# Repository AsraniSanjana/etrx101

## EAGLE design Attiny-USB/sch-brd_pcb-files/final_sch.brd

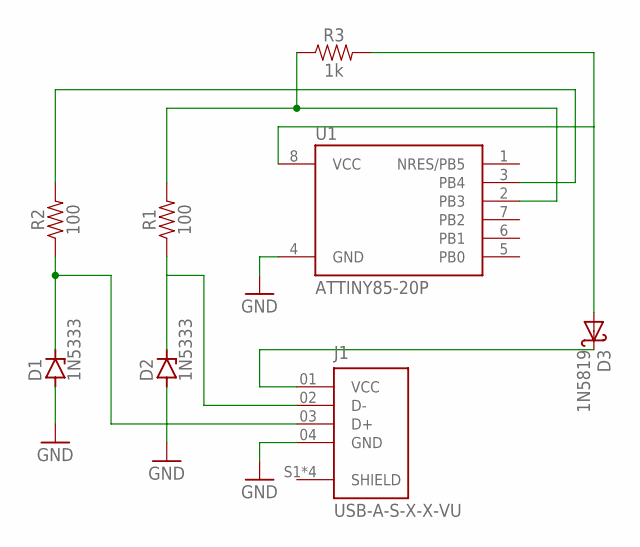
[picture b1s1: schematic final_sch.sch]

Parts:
D1, D2: 1N5333; C1702-15
D3: 1N5819; DO41-10
J1: USB-A-S-X-X-VU; SAMTEC_USB-A-S-X-X-VU
R1, R2: 100; AXIAL-0.3EZ
R3: 1k; AXIAL-0.3-KIT
U1: ATTINY85-20P; PDIP08_300MIL

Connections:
GND: D1.A, D2.A, J1.04 (GND), U1.4 (GND)
unnamed: D1.C, J1.03 (D+), R2.P$1 (1)
unnamed: D2.C, J1.02 (D-), R1.P$1 (1)
unnamed: R2.P$2 (2), U1.3 (PB4)
unnamed: R1.P$2 (2), R3.P$1 (1), U1.2 (PB3)
unnamed: D3.C, J1.01 (VCC)
unnamed: D3.A, R3.P$2 (2), U1.8 (VCC)

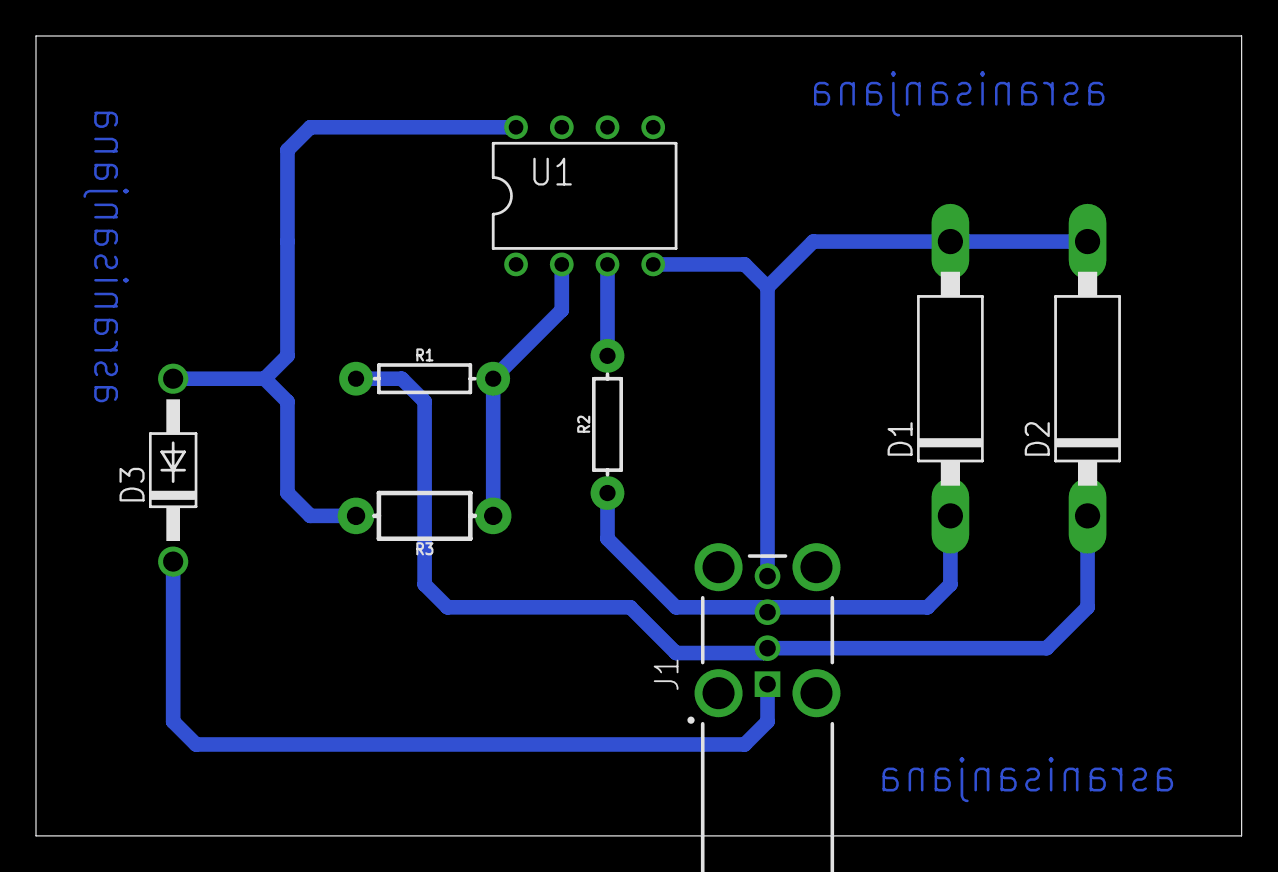
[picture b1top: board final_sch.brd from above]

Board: 2 copper layers, 67.0 x 44.4 mm, 8 parts (0 on the bottom side), 7 nets.

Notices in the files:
parts and their libraries:
SparkFun-Resistors: Licensing: Creative Commons ShareAlike 4.0 International - https://creativecommons.org/licenses/by-sa/4.0
